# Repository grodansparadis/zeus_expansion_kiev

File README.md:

<h1>Zeus Expansion Kiev</h1>

nrf24L01 add on card with Zeus expansion connector. Fits the 
<a href="http://www.grodansparadis.com/odessa/odessa.html">Odessa</a> module
among other modules.

<hr>

This project is part of the <a href="http://www.vscp.org">VSCP (Very Simple Control Protocol) project</a>. 

<hr>

This project is licensed under the 
<a href="http://creativecommons.org/licenses/by-nc-sa/3.0/">Creative Commons open source license Attribution-NonCommercial-ShareAlike 3.0 Unported</a>. 
Other license options are available by conacting <a href="malto:info@grodansparadis.com">Paradis of the Frog AB</a>

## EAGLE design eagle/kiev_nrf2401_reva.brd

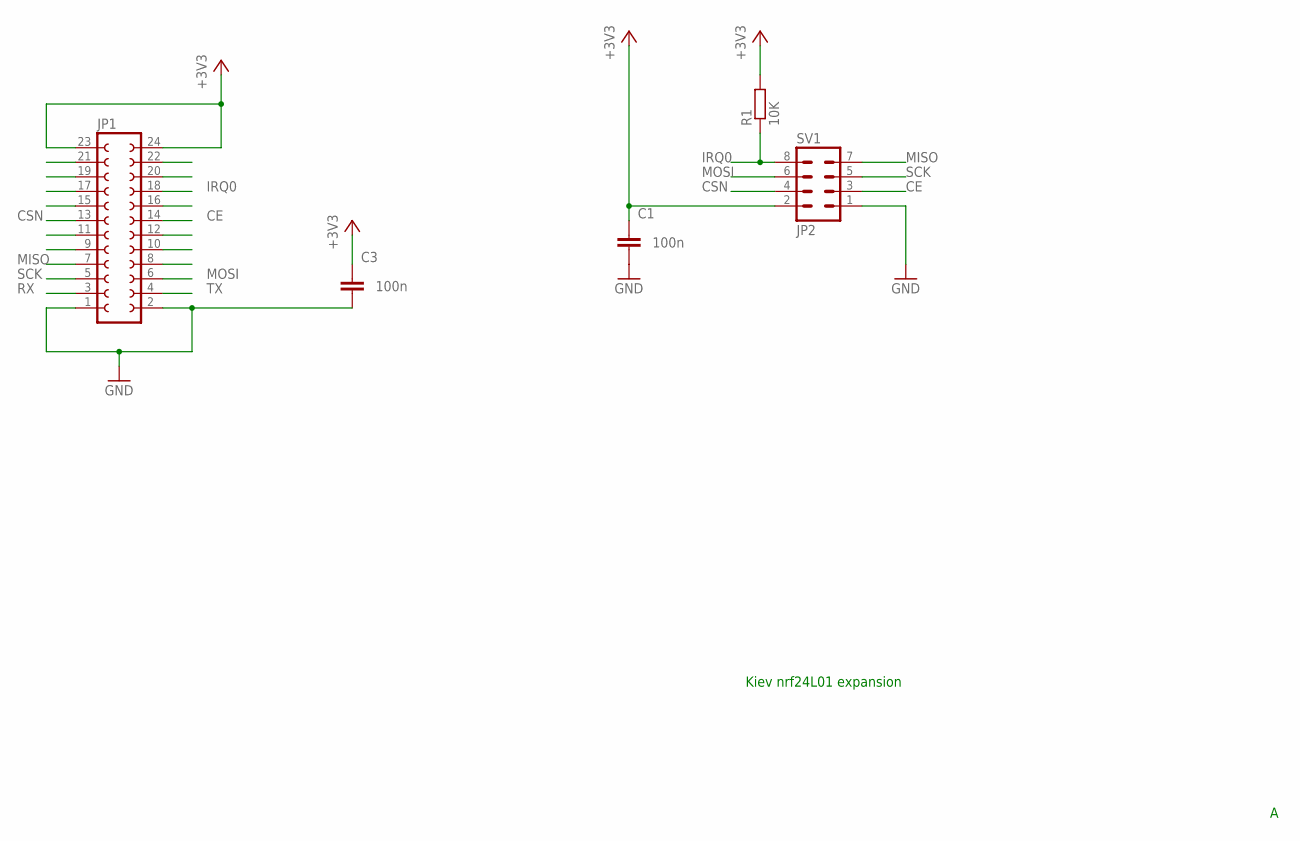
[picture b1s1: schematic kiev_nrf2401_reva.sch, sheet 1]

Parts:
C1, C3: 100n; C0805
JP1: FE12-2
R1: 10K; R0805
SV1: JP2; MA04-2

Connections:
+3V3: C1.1, C3.1, JP1.23, JP1.24, R1.2, SV1.2
CE: JP1.14, SV1.3
CSN: JP1.13, SV1.4
GND: C1.2, C3.2, JP1.1, JP1.2, SV1.1
IRQ0: JP1.18, R1.1, SV1.8
MISO: JP1.7, SV1.7
MOSI: JP1.6, SV1.6
RX: JP1.3
SCK: JP1.5, SV1.5
TX: JP1.4

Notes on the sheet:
Kiev nrf24L01 expansion

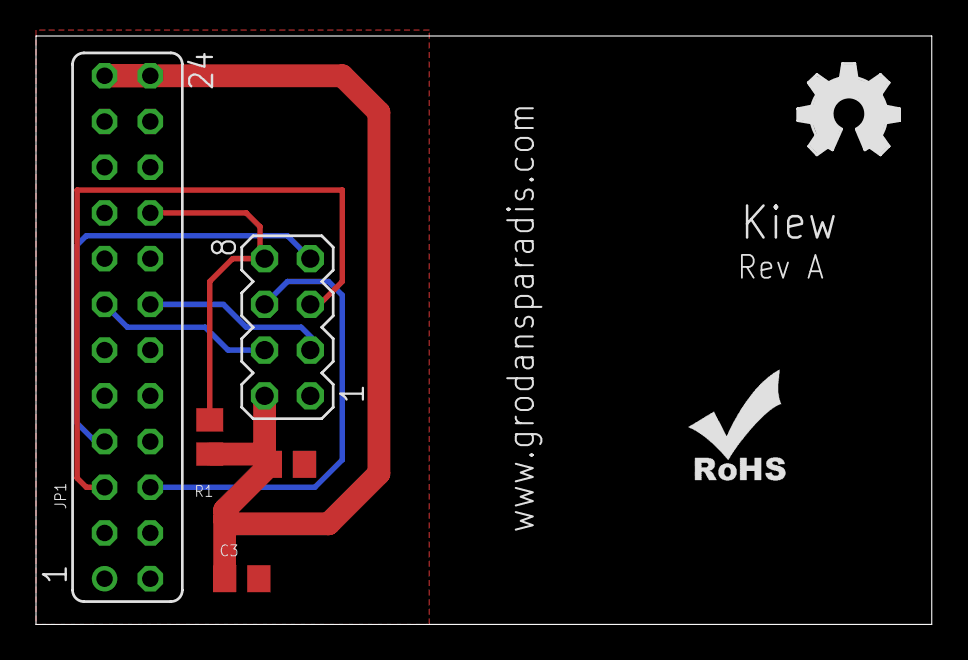
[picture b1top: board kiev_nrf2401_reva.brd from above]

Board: 2 copper layers, 49.8 x 32.7 mm, 7 parts (0 on the bottom side), 8 nets.

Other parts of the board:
U$1: OSHW_FILLX200_NOTEXT
U$2: ROHS_SILK

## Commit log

2015-11-03 Making design open
2015-12-17 Updated license and readme
